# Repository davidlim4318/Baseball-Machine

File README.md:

# Baseball-Machine
MAE 156 Capstone Project Code Files

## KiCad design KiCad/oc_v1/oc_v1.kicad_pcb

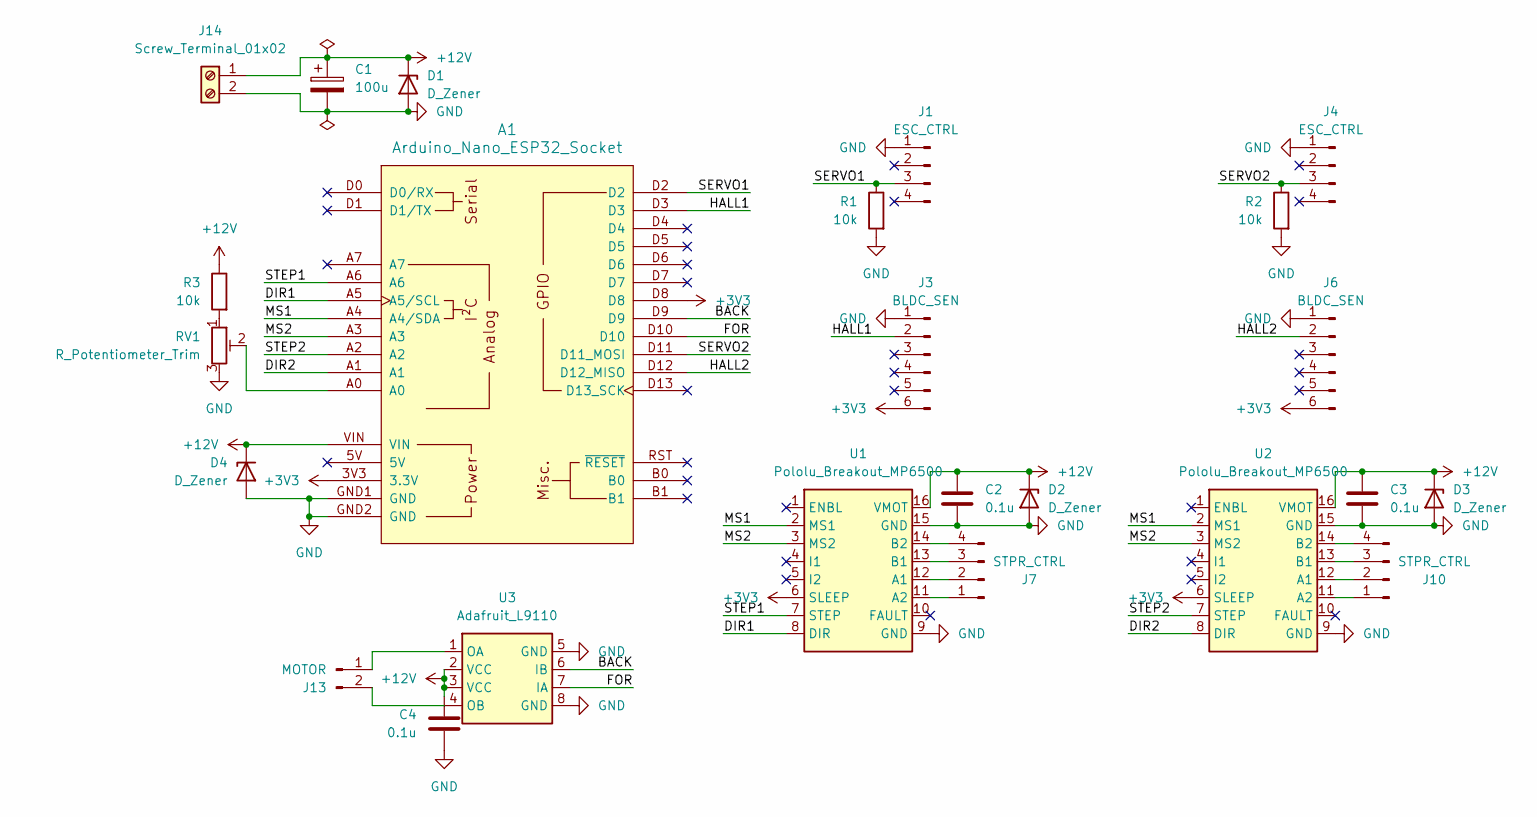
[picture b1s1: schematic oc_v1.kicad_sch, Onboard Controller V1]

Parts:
A1: Arduino_Nano_ESP32_Socket
C1: 100u; CP_Radial_D5.0mm_P2.50mm
C2, C3, C4: 0.1u; C_0603_1608Metric_Pad1.08x0.95mm_HandSolder
D1, D2, D3, D4: D_Zener; D_TUMD2
J1, J4: ESC_CTRL; JST_XH_S4B-XH-A_1x04_P2.50mm_Horizontal
J3, J6: BLDC_SEN; JST_XH_S6B-XH-A_1x06_P2.50mm_Horizontal
J7, J10: STPR_CTRL; JST_XH_S4B-XH-A_1x04_P2.50mm_Horizontal
J13: MOTOR; JST_XH_S2B-XH-A_1x02_P2.50mm_Horizontal
J14: Screw_Terminal_01x02; On_Shore_Tech_Barrier_Strip_2Pos
R1, R2, R3: 10k; R_0805_2012Metric_Pad1.20x1.40mm_HandSolder
RV1: R_Potentiometer_Trim; Bourns_TC33X_Potentiometer
U1, U2: Pololu_Breakout_MP6500
U3: Adafruit_L9110; DIP-8_W7.62mm_Socket_LongPads

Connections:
+3V3: A1.3V3 (3.3V), A1.D8, J3.6, J6.6, U1.6 (SLEEP), U2.6 (SLEEP)
+12V: A1.VIN, C1.1, C2.1, C3.1, C4.1, D1.1 (K), D2.1 (K), D3.1 (K), D4.1 (K), J14.1, R3.1, U1.16 (VMOT), U2.16 (VMOT), U3.2 (VCC), U3.3 (VCC)
/BACK: A1.D9, U3.6 (IB)
/DIR1: A1.A5 (A5/SCL), U1.8 (DIR)
/DIR2: A1.A1, U2.8 (DIR)
/FOR: A1.D10, U3.7 (IA)
/HALL1: A1.D3, J3.2
/HALL2: A1.D12 (D12_MISO), J6.2
/MS1: A1.A4 (A4/SDA), U1.2 (MS1), U2.2 (MS1)
/MS2: A1.A3, U1.3 (MS2), U2.3 (MS2)
/SERVO1: A1.D2, J1.3, R1.1
/SERVO2: A1.D11 (D11_MOSI), J4.3, R2.1
/STEP1: A1.A6, U1.7 (STEP)
/STEP2: A1.A2, U2.7 (STEP)
GND: A1.GND1 (GND), A1.GND2 (GND), C1.2, C2.2, C3.2, C4.2, D1.2 (A), D2.2 (A), D3.2 (A), D4.2 (A), J1.1, J3.1, J4.1, J6.1, J14.2, R1.2, R2.2, RV1.3, U1.9 (GND), U1.15 (GND), U2.9 (GND), U2.15 (GND), U3.5 (GND), U3.8 (GND)
unnamed: A1.A0, RV1.2
unnamed: J7.1, U1.11 (A2)
unnamed: J7.2, U1.12 (A1)
unnamed: J7.3, U1.13 (B1)
unnamed: J7.4, U1.14 (B2)
unnamed: J10.1, U2.11 (A2)
unnamed: J10.2, U2.12 (A1)
unnamed: J10.3, U2.13 (B1)
unnamed: J10.4, U2.14 (B2)
unnamed: J13.1, U3.1 (OA)
unnamed: J13.2, U3.4 (OB)
unnamed: R3.2, RV1.1

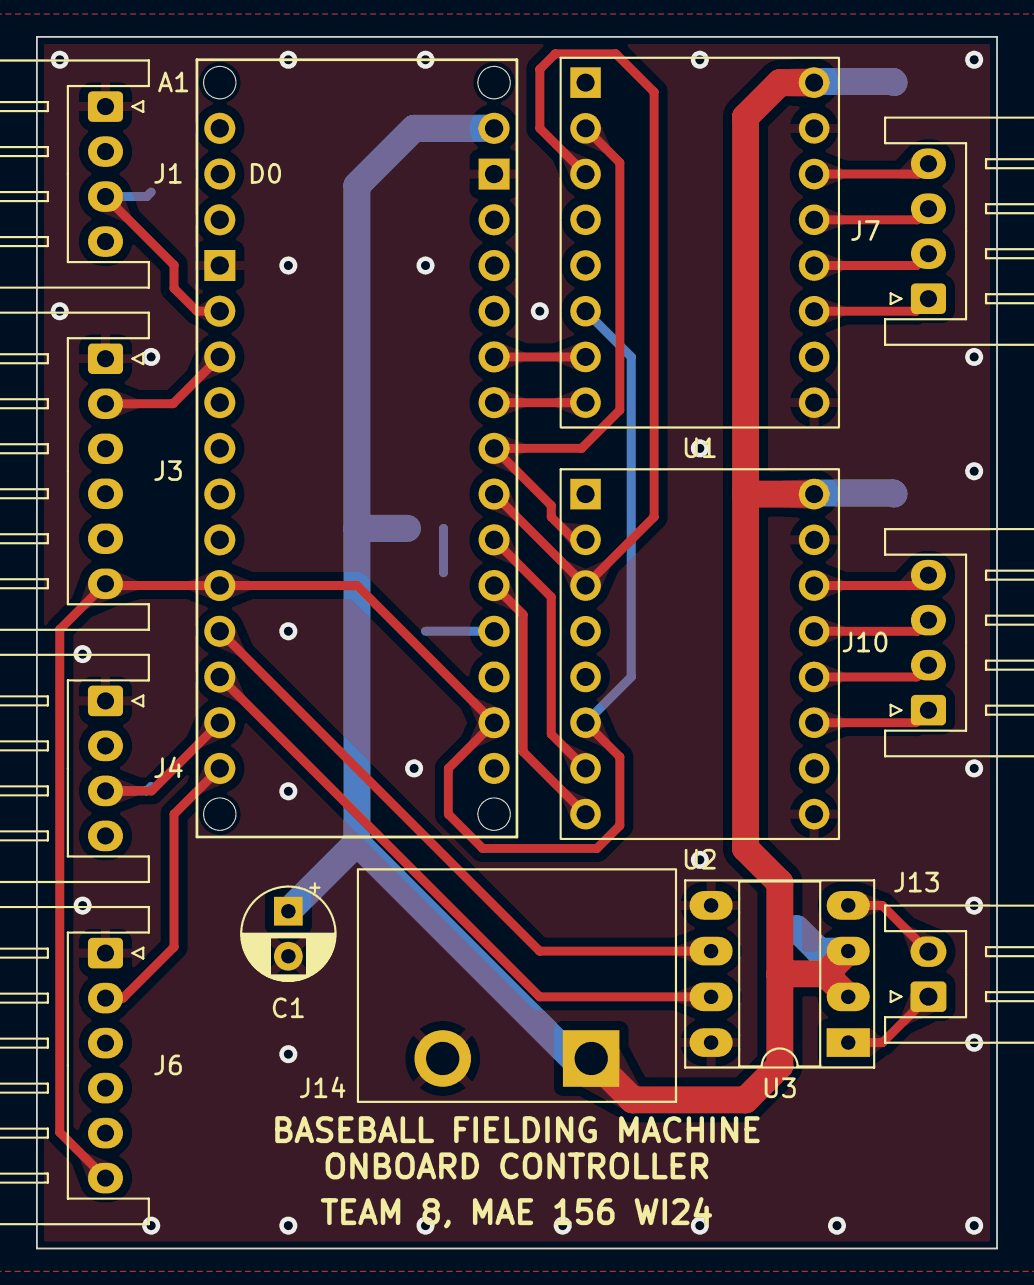
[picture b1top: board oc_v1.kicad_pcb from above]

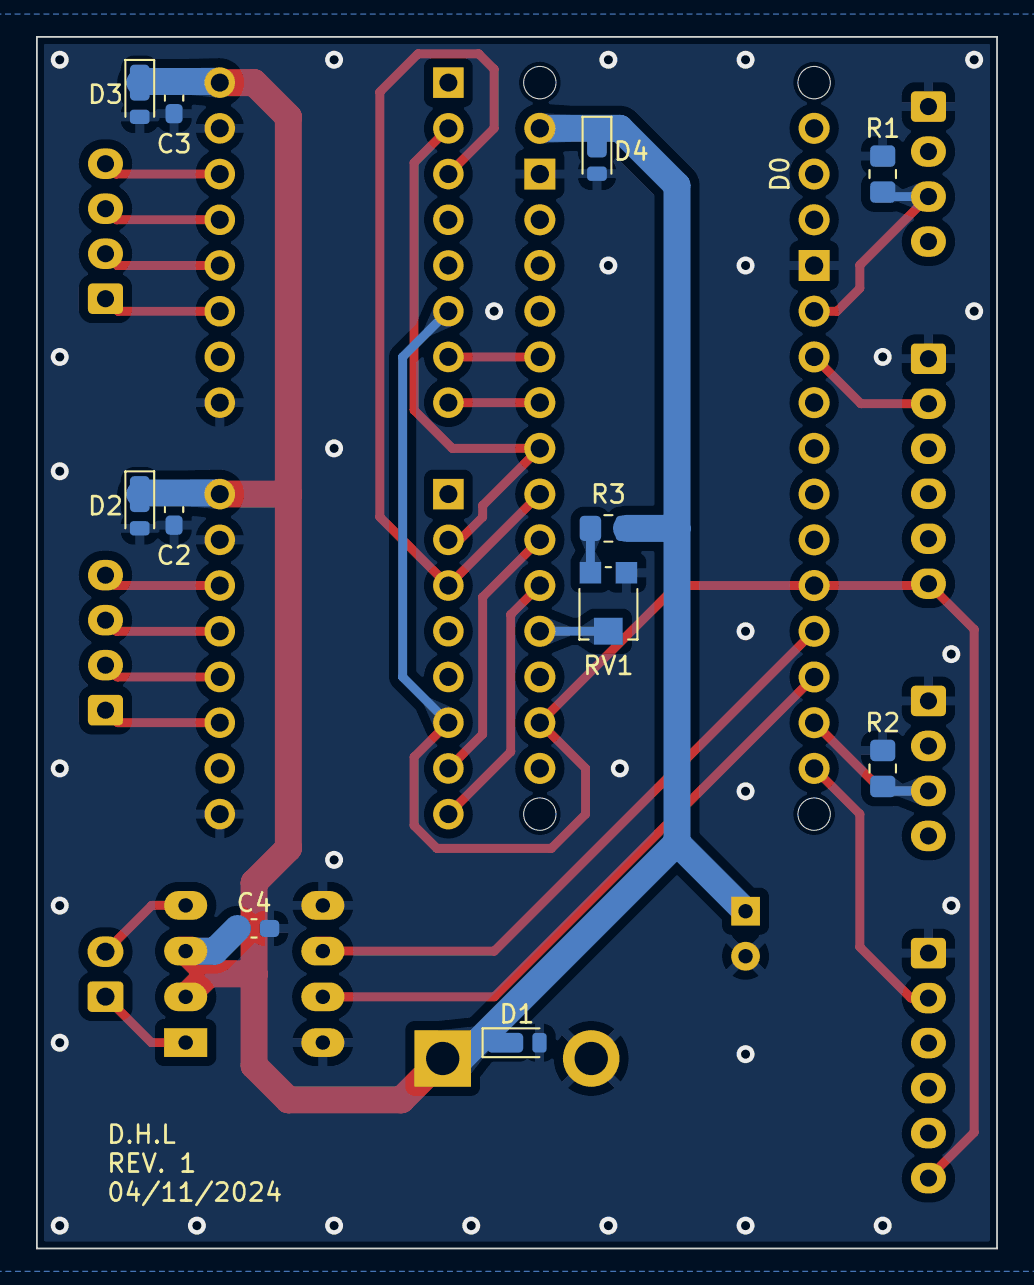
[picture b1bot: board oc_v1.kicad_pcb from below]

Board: 2 copper layers, 53.3 x 67.3 mm, 24 parts (11 on the bottom side), 27 nets.

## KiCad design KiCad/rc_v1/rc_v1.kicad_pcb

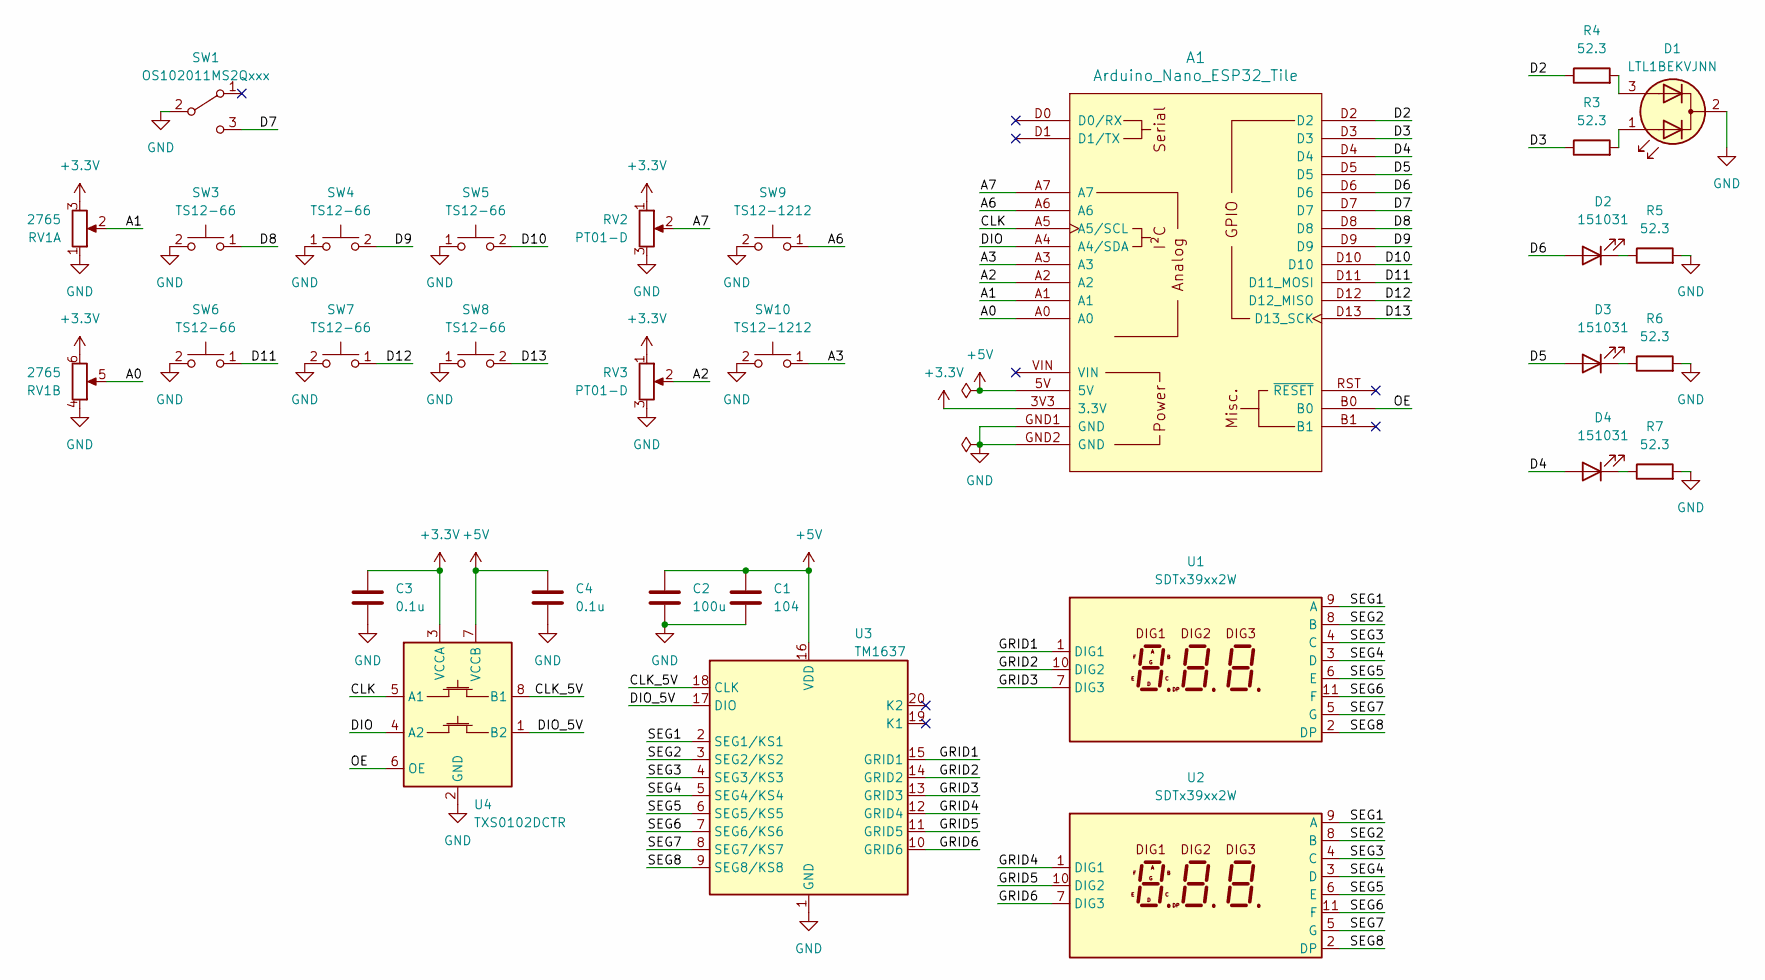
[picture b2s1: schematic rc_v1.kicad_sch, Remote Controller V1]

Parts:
A1: Arduino_Nano_ESP32_Tile
C1: 104; C_0603_1608Metric_Pad1.08x0.95mm_HandSolder
C2: 100u; C_0603_1608Metric_Pad1.08x0.95mm_HandSolder
C3, C4: 0.1u; C_0603_1608Metric_Pad1.08x0.95mm_HandSolder
D1: LTL1BEKVJNN; LED_D3.0mm-3
D2, D3, D4: 151031; LED_D3.0mm
R3, R4, R5, R6, R7: 52.3; R_0805_2012Metric_Pad1.20x1.40mm_HandSolder
RV1: 2765; Joystick_Analog_XY_Adafruit_2765
RV2, RV3: PT01-D; Potentiometer_CUI_PT01-Dxxxx-xxxx
SW1: OS102011MS2Qxxx; SW_Slide_SPDT_CK_OS102011MS2Qxxx
SW3, SW4, SW5, SW6, SW7, SW8: TS12-66; SW_PUSH_CUI_TS02-66-xxx-BK-xxx-xxx-D
SW9, SW10: TS12-1212; SW_PUSH-CUI-TS12-1212-xxx-BK-xxx-SCR-D
U1, U2: SDTx39xx2W; ChromeLED_SDTx39xx2W
U3: TM1637; SOP-20_7.5x12.8mm_P1.27mm
U4: TXS0102DCTR; SSOP-8_2.95x2.8mm_P0.65mm

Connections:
+3.3V: A1.3V3 (3.3V), C3.1, RV1.3, RV1.6, RV2.1, RV3.1, U4.3 (VCCA)
+5V: A1.5V, C1.1, C2.1, C4.1, U3.16 (VDD), U4.7 (VCCB)
/A0: A1.A0, RV1.5
/A1: A1.A1, RV1.2
/A2: A1.A2, RV3.2
/A3: A1.A3, SW10.1
/A6: A1.A6, SW9.1
/A7: A1.A7, RV2.2
/CLK: A1.A5 (A5/SCL), U4.5 (A1)
/CLK_5V: U3.18 (CLK), U4.8 (B1)
/D2: A1.D2, R4.1
/D3: A1.D3, R3.1
/D4: A1.D4, D4.2 (A)
/D5: A1.D5, D3.2 (A)
/D6: A1.D6, D2.2 (A)
/D7: A1.D7, SW1.3 (C)
/D8: A1.D8, SW3.1
/D9: A1.D9, SW4.2
/D10: A1.D10, SW5.2
/D11: A1.D11 (D11_MOSI), SW6.1
/D12: A1.D12 (D12_MISO), SW7.1
/D13: A1.D13 (D13_SCK), SW8.2
/DIO: A1.A4 (A4/SDA), U4.4 (A2)
/DIO_5V: U3.17 (DIO), U4.1 (B2)
/GRID1: U1.1 (DIG1), U3.15 (GRID1)
/GRID2: U1.10 (DIG2), U3.14 (GRID2)
/GRID3: U1.7 (DIG3), U3.13 (GRID3)
/GRID4: U2.1 (DIG1), U3.12 (GRID4)
/GRID5: U2.10 (DIG2), U3.11 (GRID5)
/GRID6: U2.7 (DIG3), U3.10 (GRID6)
/OE: A1.B0, U4.6 (OE)
/SEG1: U1.9 (A), U2.9 (A), U3.2 (SEG1/KS1)
/SEG2: U1.8 (B), U2.8 (B), U3.3 (SEG2/KS2)
/SEG3: U1.4 (C), U2.4 (C), U3.4 (SEG3/KS3)
/SEG4: U1.3 (D), U2.3 (D), U3.5 (SEG4/KS4)
/SEG5: U1.6 (E), U2.6 (E), U3.6 (SEG5/KS5)
/SEG6: U1.11 (F), U2.11 (F), U3.7 (SEG6/KS6)
/SEG7: U1.5 (G), U2.5 (G), U3.8 (SEG7/KS7)
/SEG8: U1.2 (DP), U2.2 (DP), U3.9 (SEG8/KS8)
GND: A1.GND1 (GND), A1.GND2 (GND), C1.2, C2.2, C3.2, C4.2, D1.2 (K), R5.2, R6.2, R7.2, RV1.1, RV1.4, RV2.3, RV3.3, SW1.2 (B), SW3.2, SW4.1, SW5.1, SW6.2, SW7.2, SW8.1, SW9.2, SW10.2, U3.1 (GND), U4.2 (GND)
unnamed: D1.1 (A1), R3.2
unnamed: D1.3 (A2), R4.2
unnamed: D2.1 (K), R5.1
unnamed: D3.1 (K), R6.1
unnamed: D4.1 (K), R7.1

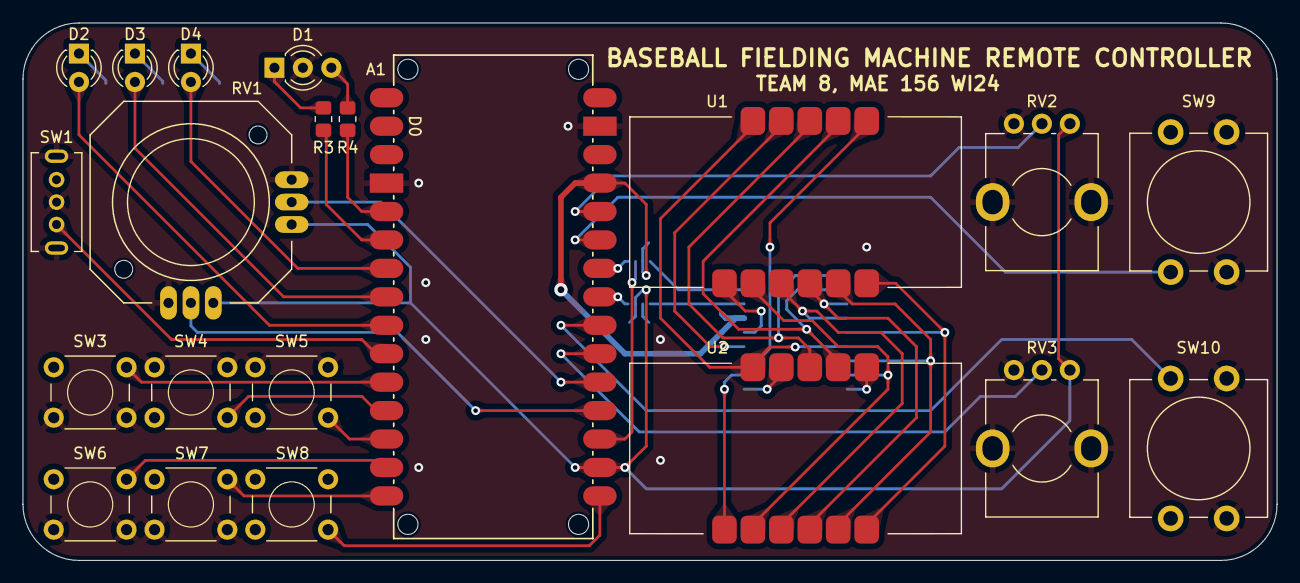
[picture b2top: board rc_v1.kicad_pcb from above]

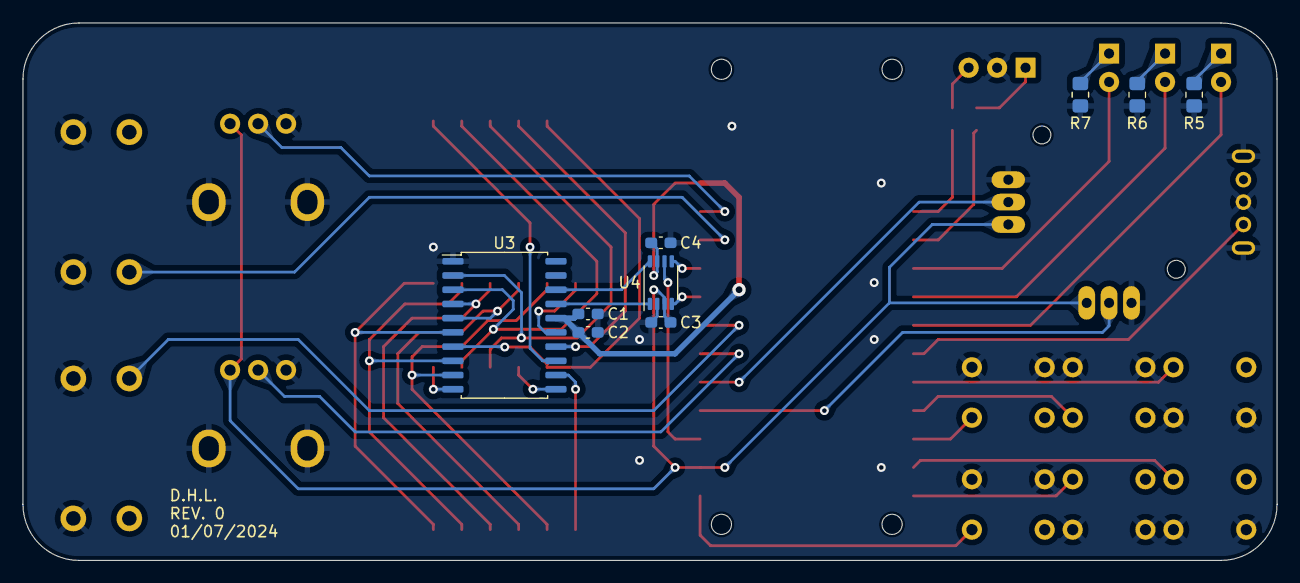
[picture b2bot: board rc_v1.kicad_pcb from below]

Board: 2 copper layers, 112.0 x 48.0 mm, 30 parts (9 on the bottom side), 45 nets.

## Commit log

2023-12-22 Added Arduino test files
2024-01-04 Remote Controller PCB Milestone 1
    Created Remote Controller PCB project, routed LED tracks
2024-01-04 Remote Controller PCB Milestone 2
    Routed right side inputs
2024-01-05 Remote Controller PCB Milestone 3
    Tentatively completed all connections
2024-01-06 Backup
    Will replace buffer with level shifter
2024-01-07 Remote Controller PCB Milestone 5
    Added level shifter IC, prototype board nearly completed
2024-01-08 Remote Controller PCB Milestone 6
    Added GPIO output to OE input pin
2024-01-10 Added some misc sketches
2024-01-12 Design v1 Finished
2024-01-12 Zipped
2024-01-12 Ready to test improved code
2024-01-31 Added new sketches, libraries, code
2024-02-04 One way communication achieved
2024-02-05 Added servo library for esp32, added motor control
2024-02-05 implemented two way communication
2024-02-17 Throttle control adjustments, added calibration script
2024-02-18 Improved code
2024-02-21 Started on onboard controller
2024-02-22 Completed onboard controller PCB
2024-03-02 fixed problem with pcb
2024-03-09 changed addresses
2024-03-09 added battery voltage checker
2024-03-10 added feeder control
2024-03-11 revised onboard pcb
2024-03-11 new arduino
2024-03-11 stepper X moves
2024-03-11 checkpoint
2024-03-14 stepper works
2024-03-14 stepper 2 looks like it works
2024-03-15 improved onboard controller
2024-03-15 new arduino (again)
2024-03-16 filtering speed output
2024-03-16 tuned
2024-03-17 minor adjustments
2024-03-17 switched wheel ports
2024-03-19 feeder update
2024-03-31 KiCad Backups
2024-04-02 Moved 156 folder
2024-04-07 MAC Address changed inexplicably
2024-04-10 MAC Address Setting
